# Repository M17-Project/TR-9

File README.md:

# TR-9
<p align='center'>

</p>

TR-9 is a handheld transceiver (HT) for the M17 standard. Its specification can be found [here](https://github.com/sp5wwp/M17_spec).
This repo contains KiCAD schematics and gerber files. 

The firmware source code has been moved to [M17-project/TR-9_firmware](https://github.com/m17-project/TR-9_firmware).
The codeplug example has been moved to [TR-9_Codeplug](https://github.com/M17-Project/codeplug)

# Capabilities
The TR-9 Radio will be capable of the following:
* UHF band (420 MHz - 450 MHz)
* Digital Voice ([M17 Codec](https://docs.m17project.org))
* FM Voice
* APRS via 1200 bps Packet (AX.25)
* Short text messaging (SMS-like)
* Optional Wi-Fi and GPS modules

# Hardware  
The heart of TR-9 is STM32F777VI microcontroller. The handheld also contains:  
*  a **DEM 128128A1 TMH-PWN** 1.44" 128x128px TFT display  
*  an **ESP8266-12F** WiFi module  
*  an **ADF7021** chip for the RF  
*  an **LSM9DS1** 9DoF sensor  
*  a USB-micro connector for firmware update (so-called *DFU mode*)  
*  a microSD card slot for codeplug and storage  
*  a connector for a GNSS module  
*  a Kenwood connector for external MIC/SPK  

RF output level can be regulated by the software. The maximum power output is 3 watts. The radio can work with both analog and digital modulation.  

# Software
M17 standard was designed having [Codec2](https://github.com/drowe67/codec2) vocoder in mind. TR-9 takes advantage of STM's internal Advanced Encryption Standard (AES) hardware for optional end-to-end encryption. There is a possibility of using other block ciphers and scrambling.  

## Pinouts

Mainboard SWD/STLink: [GND, 3v3, CLK, DIO, RST], square pad is Pin 1 and therefore GND.

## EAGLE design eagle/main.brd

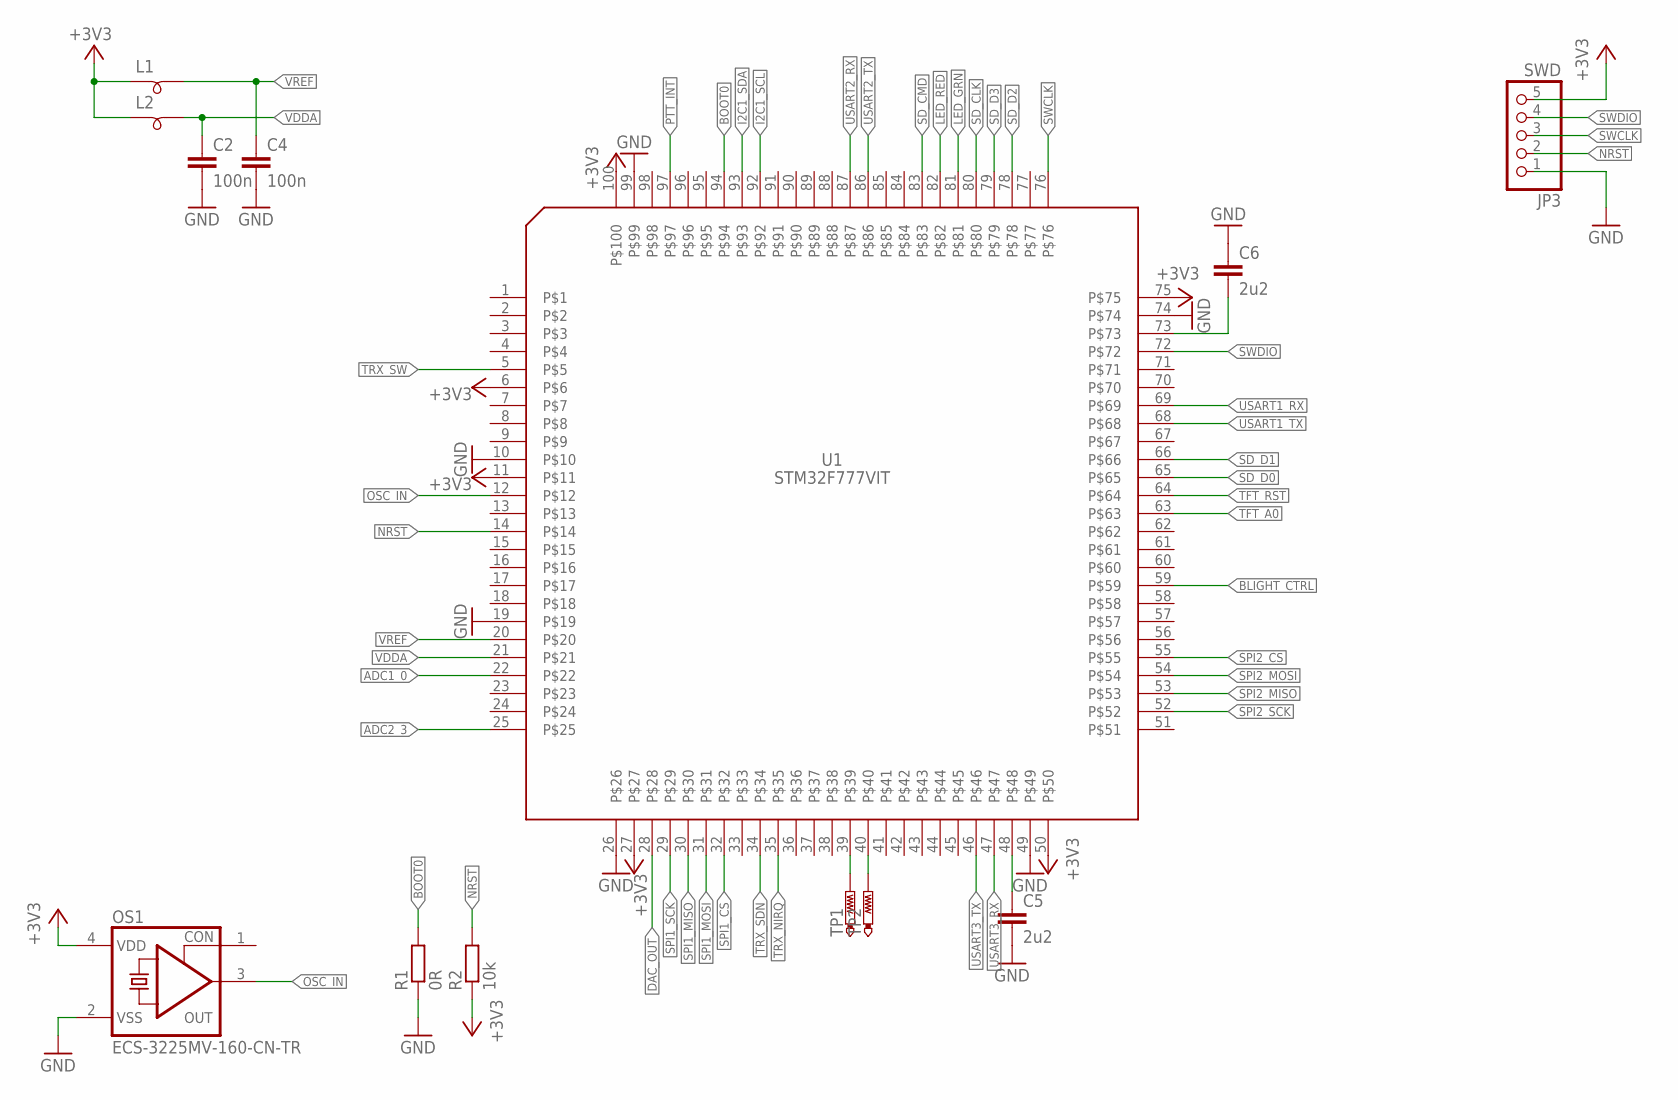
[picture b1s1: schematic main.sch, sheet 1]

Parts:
C2, C4: 100n; C0805
C5, C6: 2u2; C1206
JP3: SWD; 1X05/90
L1, L2: SM-B5
OS1: ECS-3225MV-160-CN-TR; 3.4X2.7-4-PAD
R1: 0R; R0805
R2: 10k; R0805
TP1, TP2: PTR1B1,27; B1,27
U1: STM32F777VIT; LQFP100

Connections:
+3V3: JP3.5, L1.1, L2.1, OS1.4 (VDD), R2.1, U1.6, U1.11, U1.27, U1.50, U1.75, U1.100; also elsewhere on the board
ADC1_0: U1.22; also elsewhere on the board
ADC2_3: U1.25; also elsewhere on the board
BLIGHT_CTRL: U1.59; also elsewhere on the board
BOOT0: R1.2, U1.94
DAC_OUT: U1.28; also elsewhere on the board
GND: C2.2, C4.2, C5.2, C6.1, JP3.1, OS1.2 (VSS), R1.1, U1.10, U1.19, U1.26, U1.49, U1.74, U1.99; also elsewhere on the board
I2C1_SCL: U1.92; also elsewhere on the board
I2C1_SDA: U1.93; also elsewhere on the board
LED_GRN: U1.81; also elsewhere on the board
LED_RED: U1.82; also elsewhere on the board
unnamed: C6.2, U1.73
unnamed: C5.1, U1.48
unnamed: TP1.TP, U1.39
unnamed: TP2.TP, U1.40
NRST: JP3.2, R2.2, U1.14
OSC_IN: OS1.3 (OUT), U1.12
PTT_INT: U1.97; also elsewhere on the board
SD_CLK: U1.80; also elsewhere on the board
SD_CMD: U1.83; also elsewhere on the board
SD_D0: U1.65; also elsewhere on the board
SD_D1: U1.66; also elsewhere on the board
SD_D2: U1.78; also elsewhere on the board
SD_D3: U1.79; also elsewhere on the board
SPI1_CS: U1.32; also elsewhere on the board
SPI1_MISO: U1.30
SPI1_MOSI: U1.31; also elsewhere on the board
SPI1_SCK: U1.29; also elsewhere on the board
SPI2_CS: U1.55; also elsewhere on the board
SPI2_MISO: U1.53; also elsewhere on the board
SPI2_MOSI: U1.54; also elsewhere on the board
SPI2_SCK: U1.52; also elsewhere on the board
SWCLK: JP3.3, U1.76
SWDIO: JP3.4, U1.72
TFT_A0: U1.63; also elsewhere on the board
TFT_RST: U1.64; also elsewhere on the board
TRX_NIRQ: U1.35; also elsewhere on the board
TRX_SDN: U1.34; also elsewhere on the board
TRX_SW: U1.5; also elsewhere on the board
USART1_RX: U1.69; also elsewhere on the board
USART1_TX: U1.68
USART2_RX: U1.87; also elsewhere on the board
USART2_TX: U1.86; also elsewhere on the board
USART3_RX: U1.47; also elsewhere on the board
USART3_TX: U1.46
VDDA: C2.1, L2.2, U1.21
VREF: C4.1, L1.2, U1.20

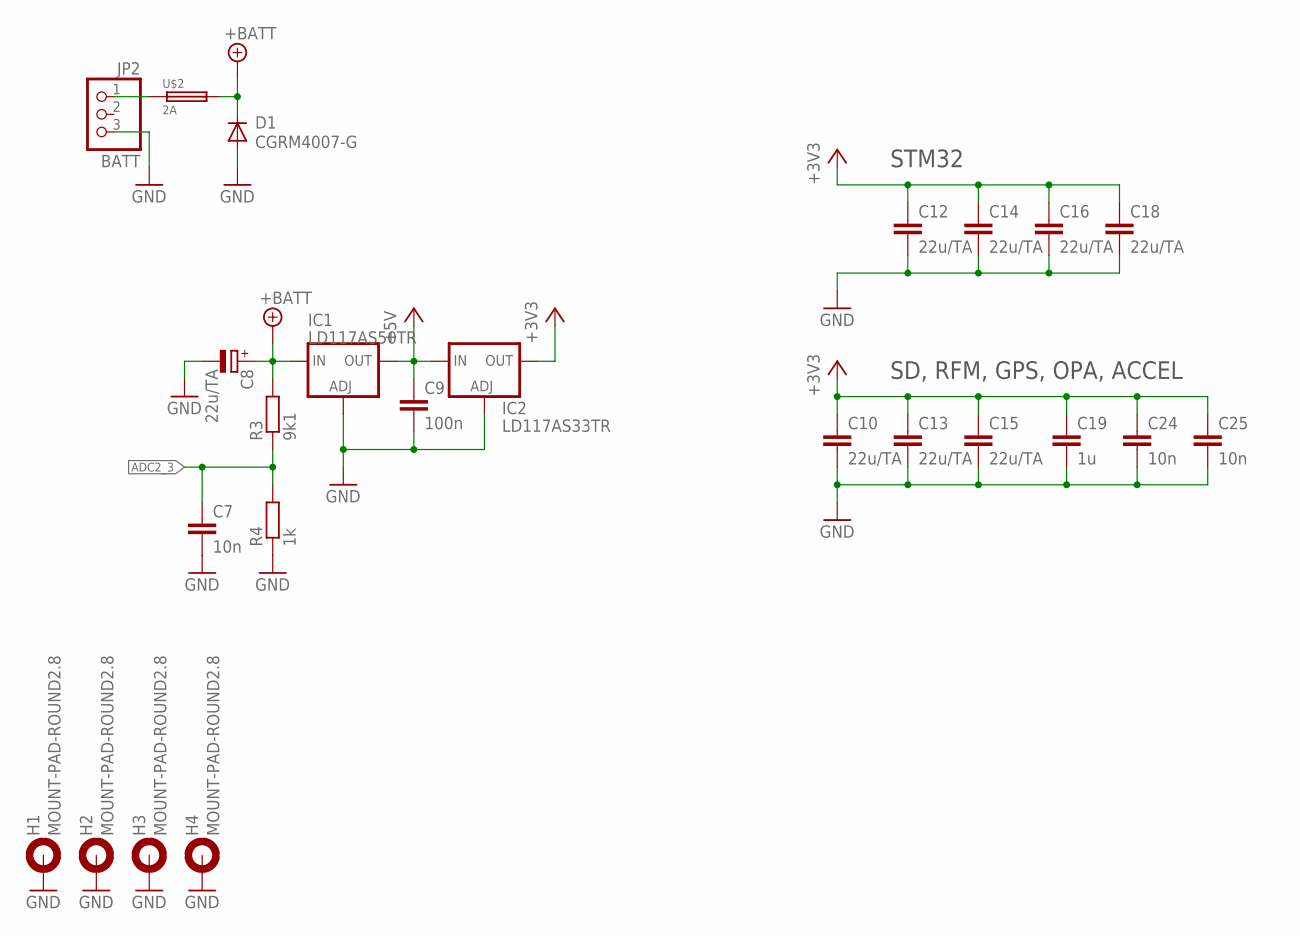
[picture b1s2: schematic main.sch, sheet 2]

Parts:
C7, C24, C25: 10n; C0805
C8: 22u/TA; SMC_C
C9: 100n; C1206
C10, C12, C13, C14, C15, C16, C18: 22u/TA; C1206
C19: 1u; C1206
D1: CGRM4007-G; SOD-123_MINI-SMA
H1, H2, H3, H4: MOUNT-PAD-ROUND2.8; 2,8-PAD
IC1: LD117AS50TR; SOT223
IC2: LD117AS33TR; SOT223
JP2: BATT; 1X03/90
R3: 9k1; R0805
R4: 1k; R0805
U$2: 2A; 1206

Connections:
+3V3: C10.1, C12.1, C13.1, C14.1, C15.1, C16.1, C18.1, C19.1, C24.1, C25.1, IC2.4 (OUT); also elsewhere on the board
+5V: C9.1, IC1.4 (OUT), IC2.3 (IN)
+BATT: C8.+, D1.C, IC1.3 (IN), R3.2, U$2.2; also elsewhere on the board
ADC2_3: C7.1, R3.1, R4.2; also elsewhere on the board
GND: C7.2, C8.-, C9.2, C10.2, C12.2, C13.2, C14.2, C15.2, C16.2, C18.2, C19.2, C24.2, C25.2, D1.A, H1.B2,8, H2.B2,8, H3.B2,8, H4.B2,8, IC1.1 (ADJ), IC2.1 (ADJ), JP2.3, R4.1; also elsewhere on the board
unnamed: JP2.1, U$2.1

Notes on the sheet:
STM32
SD, RFM, GPS, OPA, ACCEL

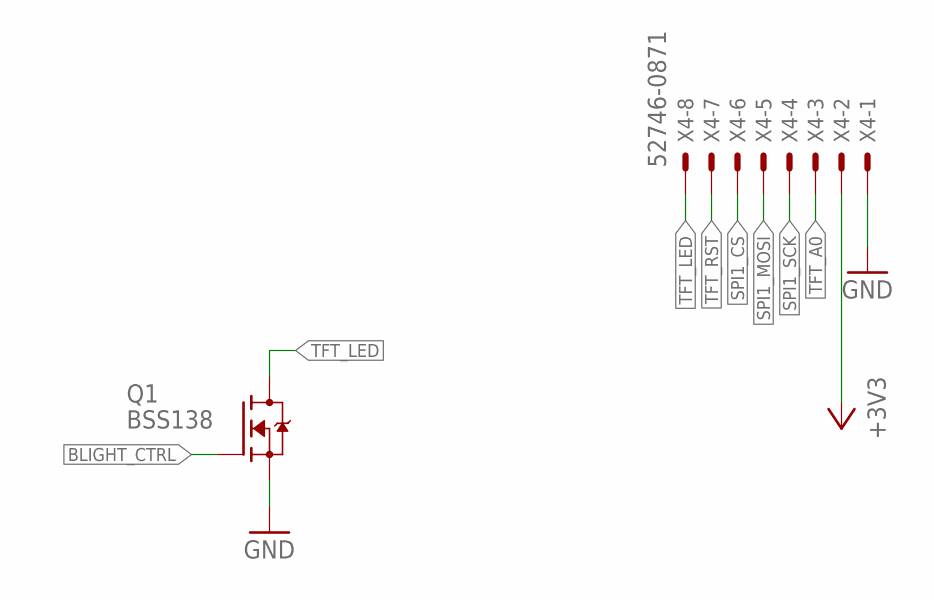
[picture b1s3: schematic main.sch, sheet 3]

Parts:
Q1: BSS138; SOT23
X4: 52746-0871; 52745-0890

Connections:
+3V3: X4.2; also elsewhere on the board
BLIGHT_CTRL: Q1.1 (G); also elsewhere on the board
GND: Q1.2 (S), X4.1; also elsewhere on the board
SPI1_CS: X4.6; also elsewhere on the board
SPI1_MOSI: X4.5; also elsewhere on the board
SPI1_SCK: X4.4; also elsewhere on the board
TFT_A0: X4.3; also elsewhere on the board
TFT_LED: Q1.3 (D), X4.8
TFT_RST: X4.7; also elsewhere on the board

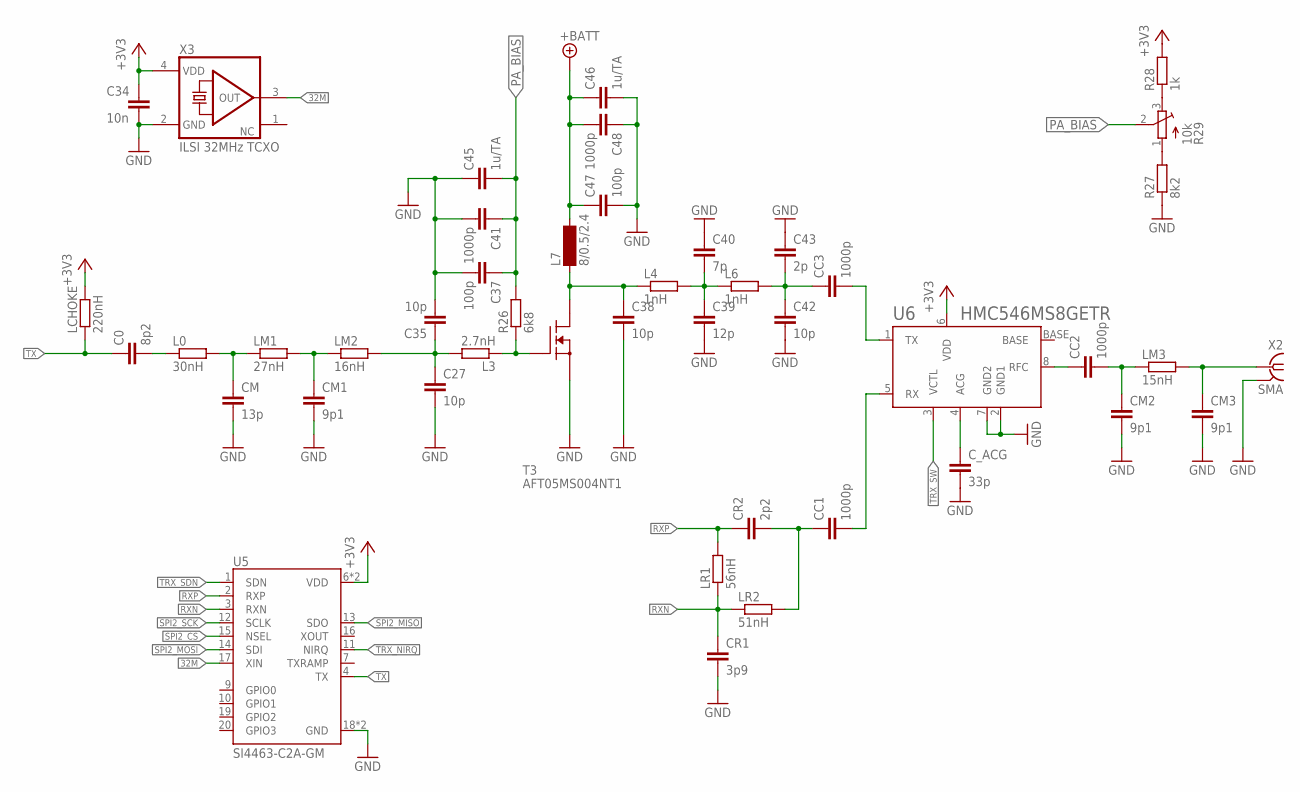
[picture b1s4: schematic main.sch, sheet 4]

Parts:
C0: 8p2; C0805
C27, C35, C38, C42: 10p; C0805
C34: 10n; C0805
C37, C47: 100p; C0805
C39: 12p; C0805
C40: 7p; C0805
C41, C48: 1000p; C0805
C43: 2p; C0805
C45, C46: 1u/TA; C1206
CC1, CC2, CC3: 1000p; C0805
CM: 13p; C0805
CM1, CM2, CM3: 9p1; C0805
CR1: 3p9; C0805
CR2: 2p2; C0805
C_ACG: 33p; C0805
L0: 30nH; R0805
L3: 2.7nH; R0805
L4, L6: 1nH; R0603
L7: 8/0.5/2.4; SM-L15B
LCHOKE: 220nH; R0805
LM1: 27nH; R0805
LM2: 16nH; R0805
LM3: 15nH; R0805
LR1: 56nH; R0805
LR2: 51nH; R0805
R26: 6k8; R0805
R27: 8k2; R0805
R28: 1k; R0805
R29: 10k; 3223W
T3: AFT05MS004NT1; SOT89-BCE
U5: SI4463-C2A-GM; QFN50P400X400X90-20N
U6: HMC546MS8GETR; SOP65P490X110-8N
X2: SMA; J502-ND-142-0701-871/876
X3: ILSI 32MHz TCXO; ASE

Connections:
32M: U5.17 (XIN), X3.3 (OUT)
+3V3: C34.1, LCHOKE.2, R28.2, U5.6 (VDD), U5.8 (VDD), U6.6 (VDD), X3.4 (VDD); also elsewhere on the board
+BATT: C46.1, C47.1, C48.2, L7.2; also elsewhere on the board
GND: C27.2, C34.2, C35.2, C37.2, C38.2, C39.2, C40.1, C41.2, C42.2, C43.1, C45.1, C46.2, C47.2, C48.1, CM.2, CM1.2, CM2.2, CM3.2, CR1.2, C_ACG.2, R27.1, T3.S, U5.18 (GND), U5.21 (GND), U6.2 (GND1), U6.7 (GND2), X2.G@1 (2), X2.G@2 (2), X2.G@3 (2), X2.G@4 (2), X3.2 (GND); also elsewhere on the board
unnamed: CC3.2, U6.1 (TX)
unnamed: C27.1, C35.1, L3.2, LM2.2
unnamed: CM3.1, LM3.2, X2.1
unnamed: CC2.2, CM2.1, LM3.1
unnamed: C0.2, L0.1
unnamed: CM.1, L0.2, LM1.1
unnamed: CM1.1, LM1.2, LM2.1
unnamed: R27.2, R29.1 (A)
unnamed: CC1.1, CR2.2, LR2.2
unnamed: L3.1, R26.1, T3.G
unnamed: CC1.2, U6.5 (RX)
unnamed: CC2.1, U6.8 (RFC)
unnamed: C_ACG.1, U6.4 (ACG)
unnamed: R28.1, R29.3 (E)
unnamed: C38.1, L4.1, L7.1, T3.D
unnamed: C39.1, C40.2, L4.2, L6.1
unnamed: C42.1, C43.2, CC3.1, L6.2
PA_BIAS: C37.1, C41.1, C45.2, R26.2, R29.2 (S)
RXN: CR1.1, LR1.1, LR2.1, U5.3 (RXN)
RXP: CR2.1, LR1.2, U5.2 (RXP)
SPI2_CS: U5.15 (NSEL); also elsewhere on the board
SPI2_MISO: U5.13 (SDO); also elsewhere on the board
SPI2_MOSI: U5.14 (SDI); also elsewhere on the board
SPI2_SCK: U5.12 (SCLK); also elsewhere on the board
TRX_NIRQ: U5.11 (NIRQ); also elsewhere on the board
TRX_SDN: U5.1 (SDN); also elsewhere on the board
TRX_SW: U6.3 (VCTL); also elsewhere on the board
TX: C0.1, LCHOKE.1, U5.4 (TX)

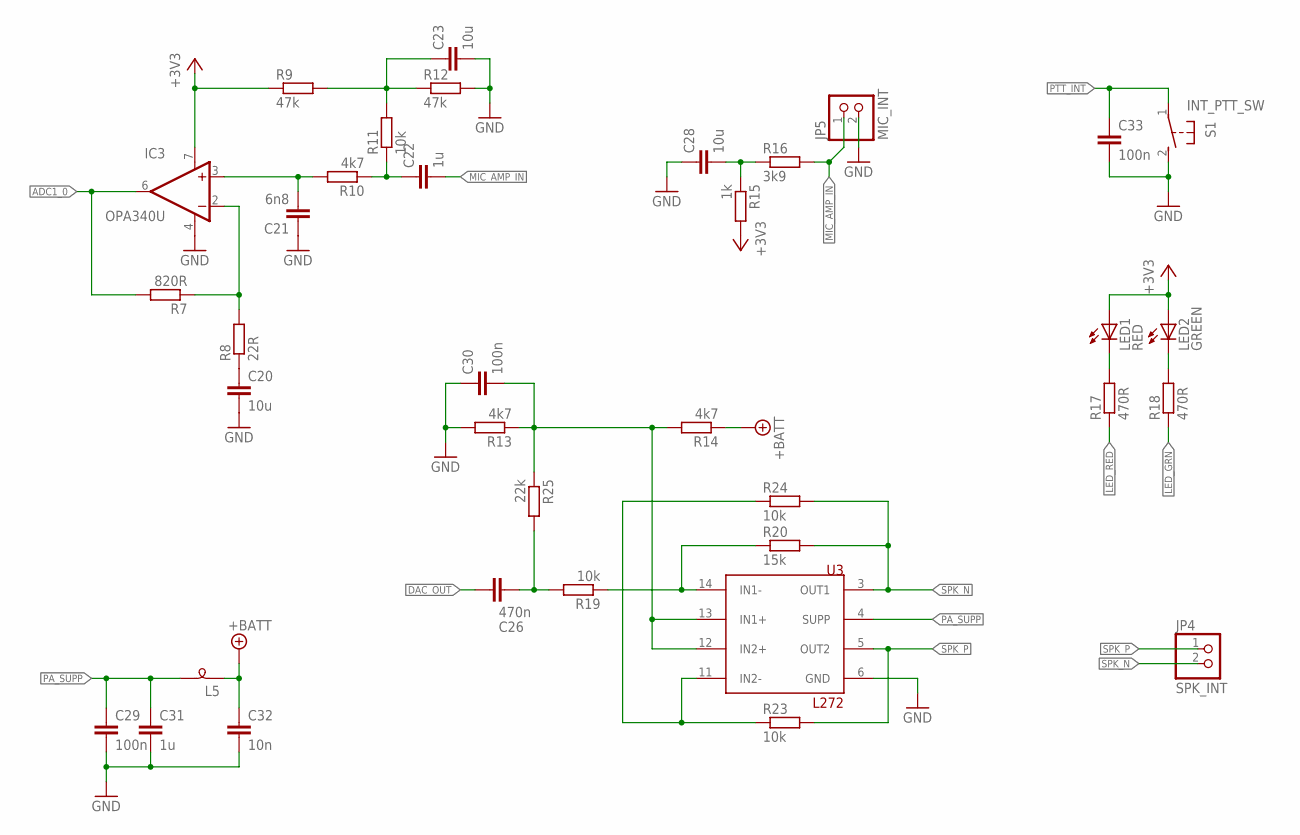
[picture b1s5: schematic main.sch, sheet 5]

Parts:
C20, C23, C28: 10u; C1206
C21: 6n8; C0805
C22, C31: 1u; C1206
C26: 470n; C0805
C29, C30: 100n; C1206
C32: 10n; C0805
C33: 100n; C0805
IC3: OPA340U; SO08
JP4: SPK_INT; 1X02
JP5: MIC_INT; 1X02
L5: SM-B5
LED1: RED; CHIPLED_1206
LED2: GREEN; CHIPLED_1206
R7: 820R; R0805
R8: 22R; R0805
R9, R12: 47k; R0805
R10, R13, R14: 4k7; R0805
R11, R19, R23, R24: 10k; R0805
R15: 1k; R0805
R16: 3k9; R0805
R17, R18: 470R; R0805
R20: 15k; R0805
R25: 22k; R0805
S1: INT_PTT_SW; B3F-31XX
U3: L272; SO16

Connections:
+3V3: IC3.7 (V+), LED1.A, LED2.A, R9.1, R15.2; also elsewhere on the board
+BATT: C32.1, L5.1, R14.1; also elsewhere on the board
ADC1_0: IC3.6 (OUT), R7.2; also elsewhere on the board
DAC_OUT: C26.1; also elsewhere on the board
GND: C20.2, C21.1, C23.2, C28.1, C29.2, C30.1, C31.2, C32.2, C33.2, IC3.4 (V-), JP5.2, R12.2, R13.2, S1.2 (S), U3.6 (GND); also elsewhere on the board
LED_GRN: R18.1; also elsewhere on the board
LED_RED: R17.1; also elsewhere on the board
MIC_AMP_IN: C22.2, JP5.1, R16.2
unnamed: R19.1, R20.1, U3.14 (IN1-)
unnamed: IC3.2 (-IN), R7.1, R8.2
unnamed: C22.1, R10.1, R11.1
unnamed: C20.1, R8.1
unnamed: LED1.C, R17.2
unnamed: LED2.C, R18.2
unnamed: R23.1, R24.1, U3.11 (IN2-)
unnamed: C26.2, R19.2, R25.2
unnamed: C28.2, R15.1, R16.1
unnamed: C21.2, IC3.3 (+IN), R10.2
unnamed: C23.1, R9.2, R11.2, R12.1
unnamed: C30.2, R13.1, R14.2, R25.1, U3.12 (IN2+), U3.13 (IN1+)
PA_SUPP: C29.1, C31.1, L5.2, U3.4 (SUPP)
PTT_INT: C33.1, S1.1; also elsewhere on the board
SPK_N: JP4.2, R20.2, R24.2, U3.3 (OUT1)
SPK_P: JP4.1, R23.2, U3.5 (OUT2)

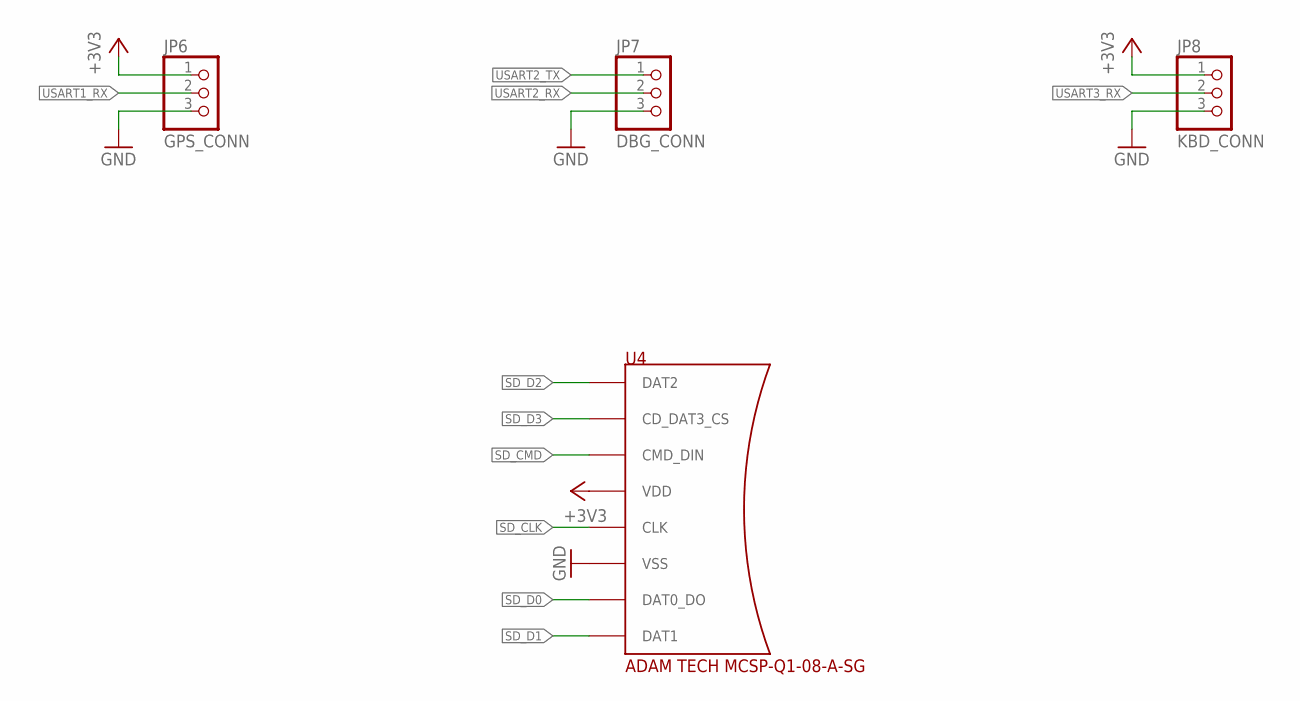
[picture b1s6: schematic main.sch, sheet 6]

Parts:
JP6: GPS_CONN; 1X03
JP7: DBG_CONN; 1X03
JP8: KBD_CONN; 1X03
U4: ADAM TECH MCSP-Q1-08-A-SG; MICROSD-PUSH-OUT

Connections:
+3V3: JP6.1, JP8.1, U4.4 (VDD); also elsewhere on the board
GND: JP6.3, JP7.3, JP8.3, U4.6 (VSS), U4.G1 (VSS), U4.G2 (VSS), U4.G3 (VSS), U4.G4 (VSS); also elsewhere on the board
SD_CLK: U4.5 (CLK); also elsewhere on the board
SD_CMD: U4.3 (CMD_DIN); also elsewhere on the board
SD_D0: U4.7 (DAT0_DO); also elsewhere on the board
SD_D1: U4.8 (DAT1); also elsewhere on the board
SD_D2: U4.1 (DAT2); also elsewhere on the board
SD_D3: U4.2 (CD_DAT3_CS); also elsewhere on the board
USART1_RX: JP6.2; also elsewhere on the board
USART2_RX: JP7.2; also elsewhere on the board
USART2_TX: JP7.1; also elsewhere on the board
USART3_RX: JP8.2; also elsewhere on the board

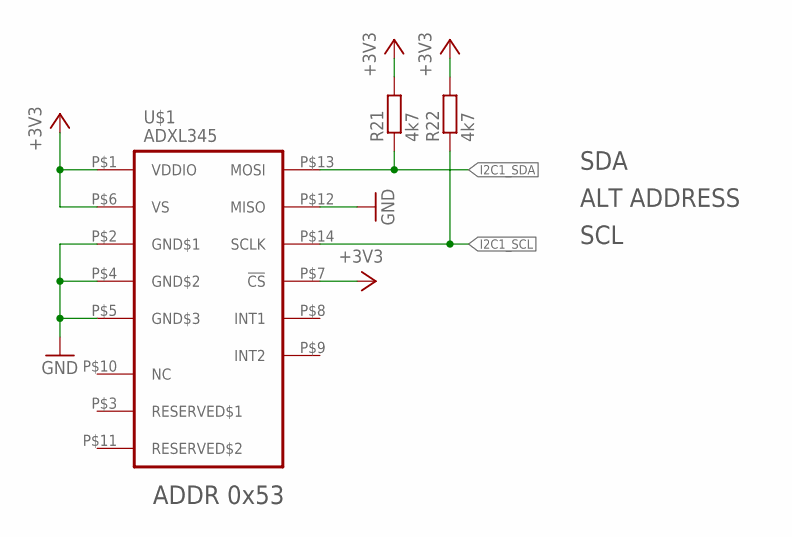
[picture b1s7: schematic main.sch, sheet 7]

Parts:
R21, R22: 4k7; R0805
U$1: ADXL345; LGA14

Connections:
+3V3: R21.2, R22.2, U$1.P$1 (VDDIO), U$1.P$6 (VS), U$1.P$7 (!CS); also elsewhere on the board
GND: U$1.P$2 (GND$1), U$1.P$4 (GND$2), U$1.P$5 (GND$3), U$1.P$12 (MISO); also elsewhere on the board
I2C1_SCL: R22.1, U$1.P$14 (SCLK); also elsewhere on the board
I2C1_SDA: R21.1, U$1.P$13 (MOSI); also elsewhere on the board

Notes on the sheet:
ALT ADDRESS
SDA
SCL
ADDR 0x53

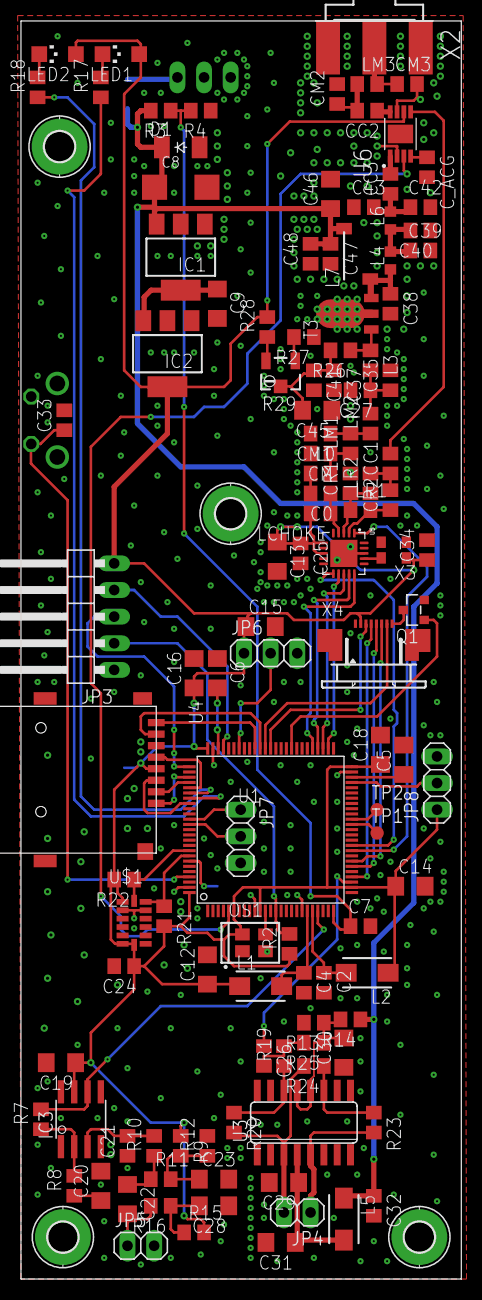
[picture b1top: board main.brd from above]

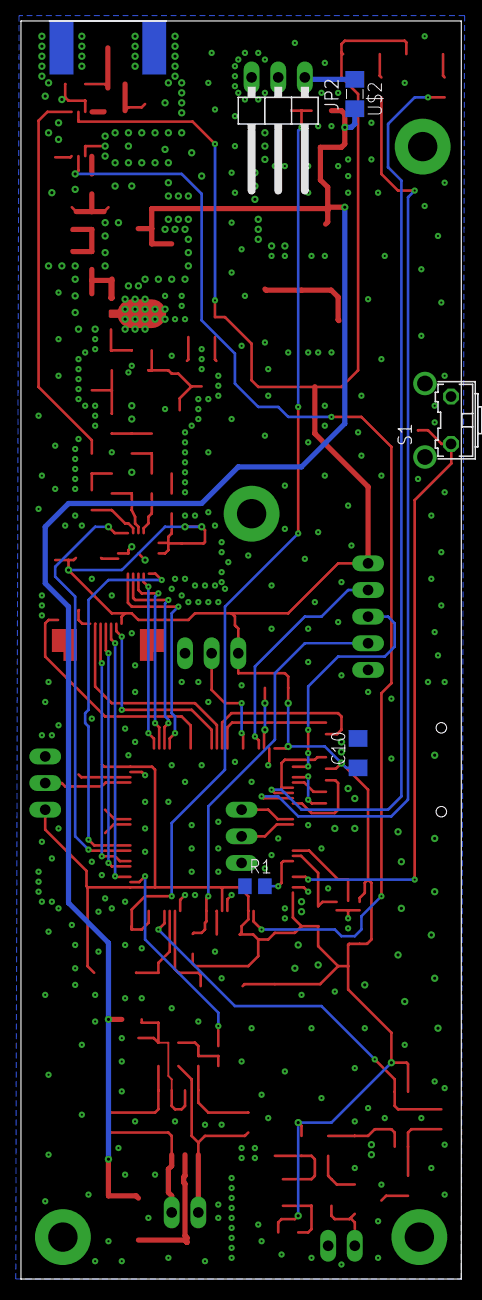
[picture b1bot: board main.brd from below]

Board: 2 copper layers, 42.0 x 120.0 mm, 127 parts (5 on the bottom side), 86 nets.

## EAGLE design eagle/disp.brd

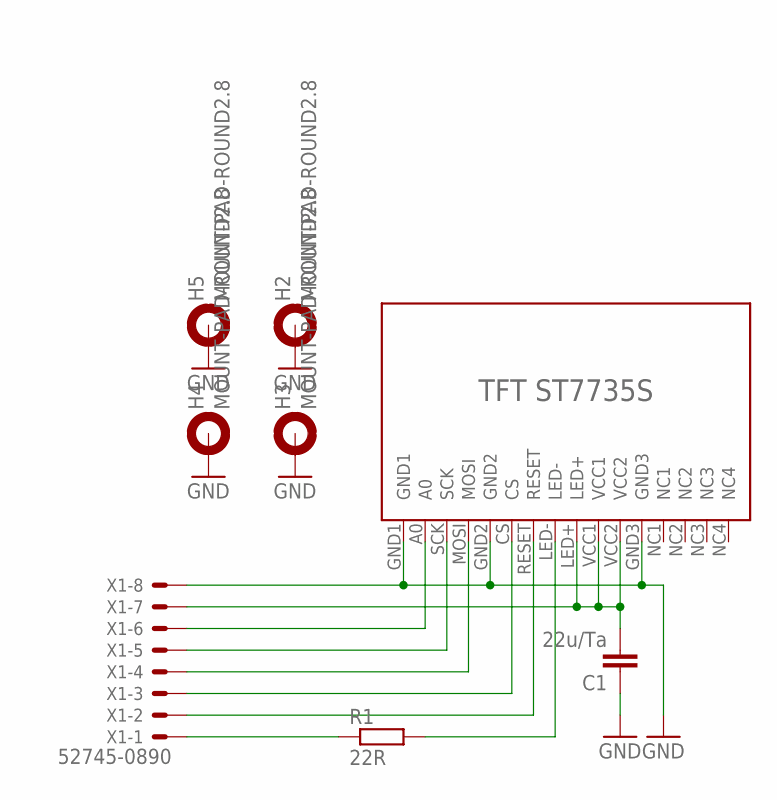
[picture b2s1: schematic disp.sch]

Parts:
C1: 22u/Ta; C1206
H2, H3, H4, H5: MOUNT-PAD-ROUND2.8; 2,8-PAD
R1: 22R; R0805
U$1: TFT_ST7735S
X1: 52745-0890

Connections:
GND: C1.1, H2.B2,8, H3.B2,8, H4.B2,8, H5.B2,8, U$1.GND1, U$1.GND2, U$1.GND3, X1.8
unnamed: C1.2, U$1.LED+, U$1.VCC1, U$1.VCC2, X1.7
unnamed: U$1.A0, X1.6
unnamed: U$1.SCK, X1.5
unnamed: U$1.MOSI, X1.4
unnamed: U$1.CS, X1.3
unnamed: U$1.RESET, X1.2
unnamed: R1.1, X1.1
unnamed: R1.2, U$1.LED-

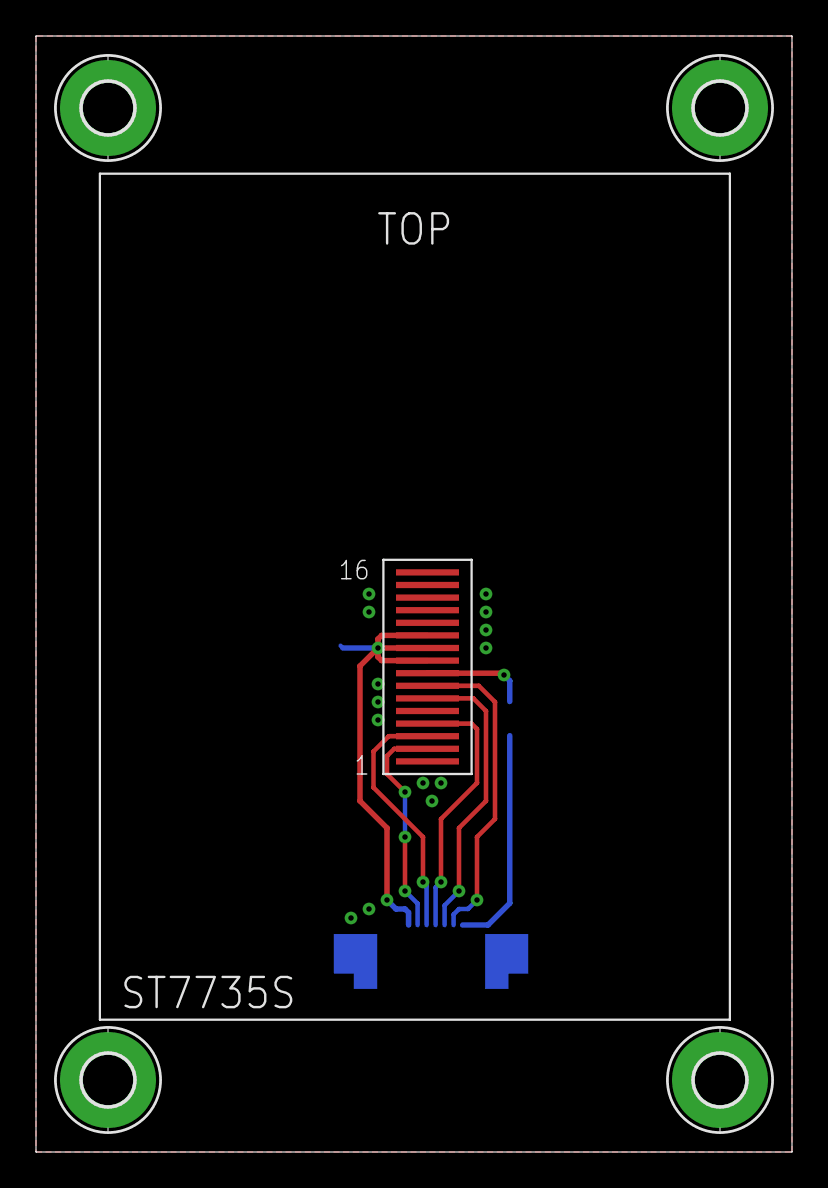
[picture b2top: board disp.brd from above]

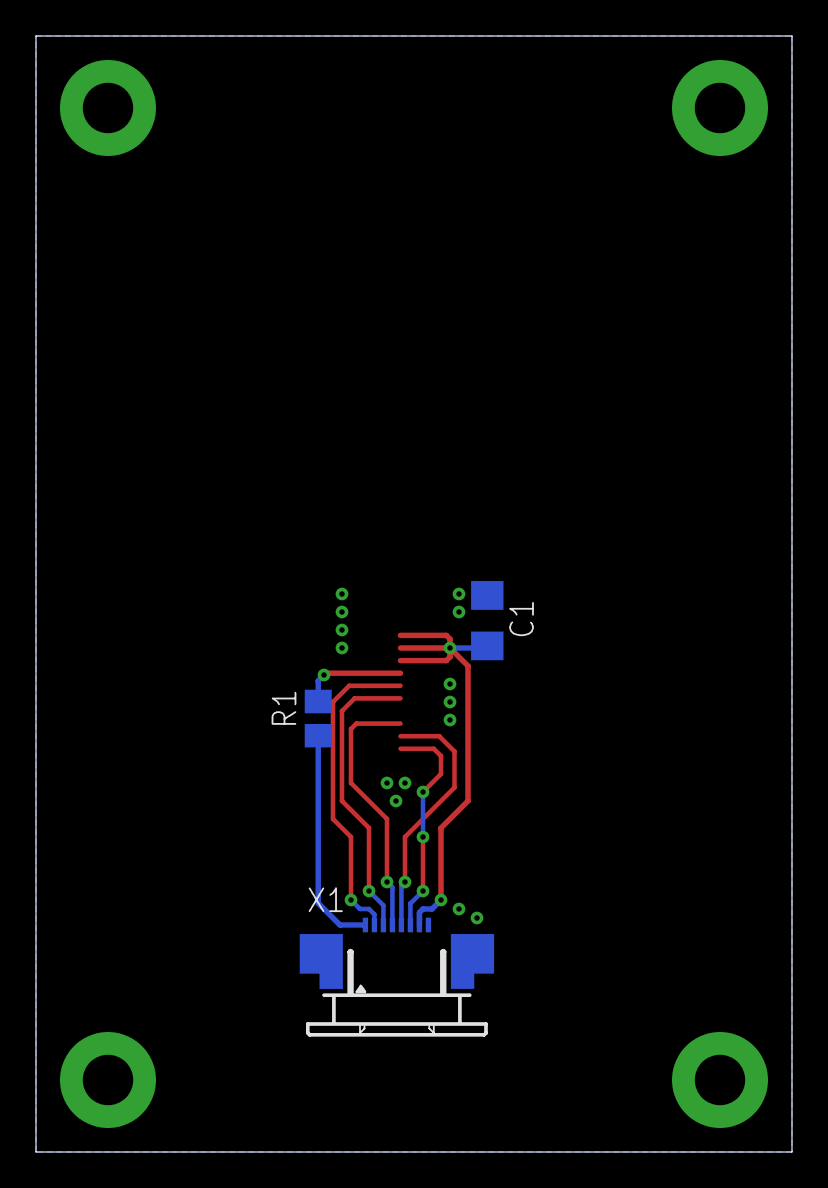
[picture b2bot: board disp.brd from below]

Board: 2 copper layers, 42.0 x 62.0 mm, 8 parts (3 on the bottom side), 9 nets.

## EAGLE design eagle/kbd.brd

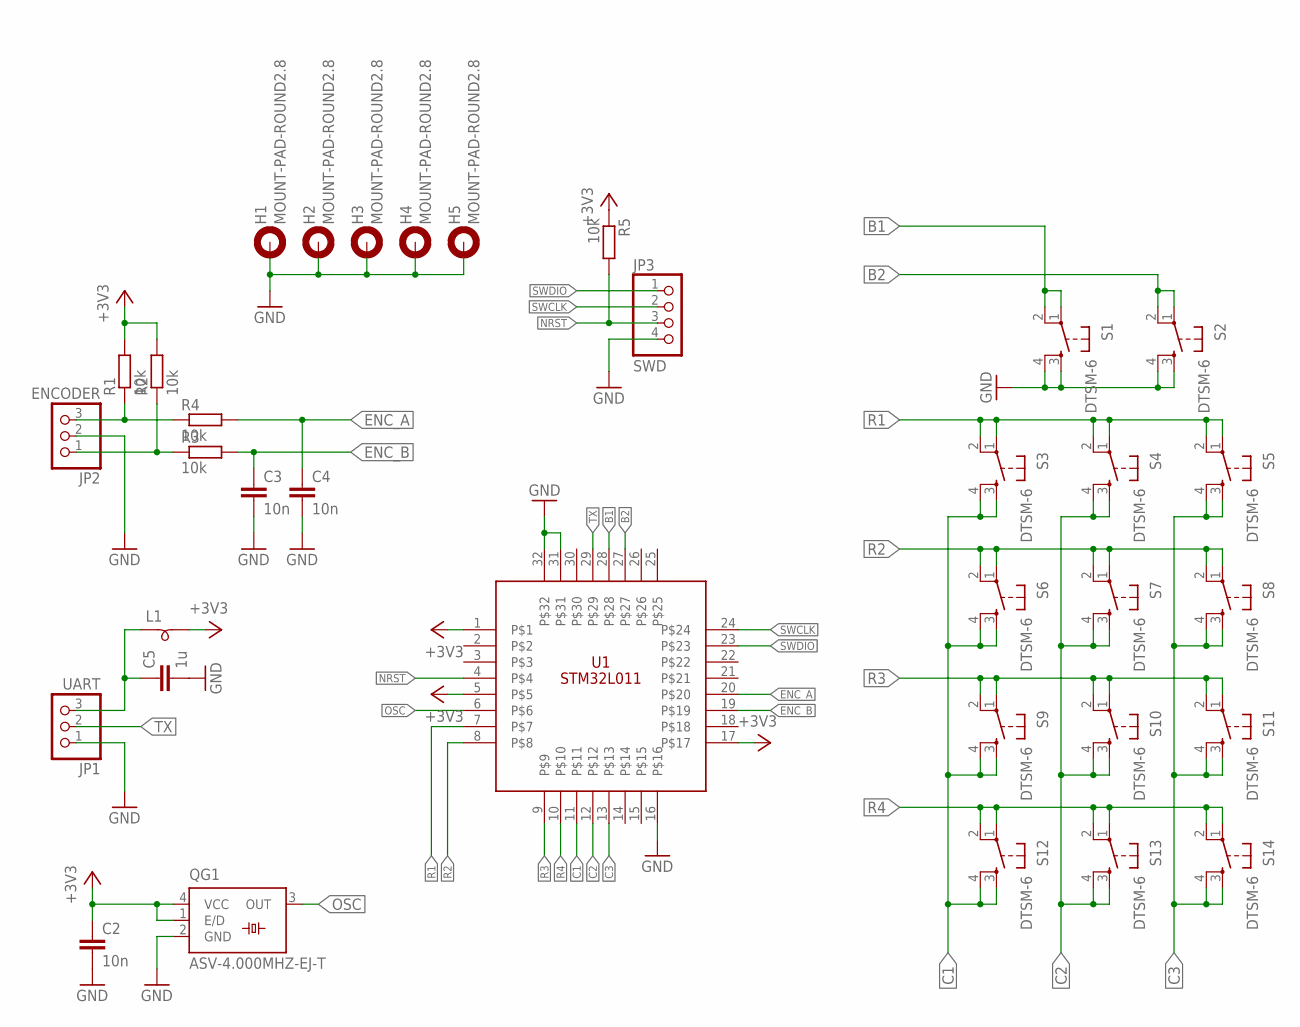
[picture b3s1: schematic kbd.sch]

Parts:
C2, C3, C4: 10n; C0805
C5: 1u; C1206
H1, H2, H3, H4, H5: MOUNT-PAD-ROUND2.8; 2,8-PAD
JP1: UART; 1X03
JP2: ENCODER; 1X03
JP3: SWD; 1X04
L1: SM-B5
QG1: ASV-4.000MHZ-EJ-T; SM77H
R1, R2, R3, R4, R5: 10k; R0805
S1, S2, S3, S4, S5, S6, S7, S8, S9, S10, S11, S12, S13, S14: DTSM-6
U1: STM32L011; LQFP32-7X7

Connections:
+3V3: C2.1, L1.2, QG1.1 (E/D), QG1.4 (VCC), R1.2, R2.2, R5.1, U1.1, U1.5, U1.17
B1: S1.1, S1.2, U1.28
B2: S2.1, S2.2, U1.27
C1: S3.3, S3.4, S6.3, S6.4, S9.3, S9.4, S12.3, S12.4, U1.11
C2: S4.3, S4.4, S7.3, S7.4, S10.3, S10.4, S13.3, S13.4, U1.12
C3: S5.3, S5.4, S8.3, S8.4, S11.3, S11.4, S14.3, S14.4, U1.13
ENC_A: C4.1, R4.2, U1.20
ENC_B: C3.1, R3.2, U1.19
GND: C2.2, C3.2, C4.2, C5.2, H1.B2,8, H2.B2,8, H3.B2,8, H4.B2,8, H5.B2,8, JP1.1, JP2.2, JP3.4, QG1.2 (GND), S1.3, S1.4, S2.3, S2.4, U1.16, U1.31, U1.32
unnamed: JP2.3, R1.1, R4.1
unnamed: JP2.1, R2.1, R3.1
unnamed: C5.1, JP1.3, L1.1
NRST: JP3.3, R5.2, U1.4
OSC: QG1.3 (OUT), U1.6
R1: S3.1, S3.2, S4.1, S4.2, S5.1, S5.2, U1.7
R2: S6.1, S6.2, S7.1, S7.2, S8.1, S8.2, U1.8
R3: S9.1, S9.2, S10.1, S10.2, S11.1, S11.2, U1.9
R4: S12.1, S12.2, S13.1, S13.2, S14.1, S14.2, U1.10
SWCLK: JP3.2, U1.24
SWDIO: JP3.1, U1.23
TX: JP1.2, U1.29

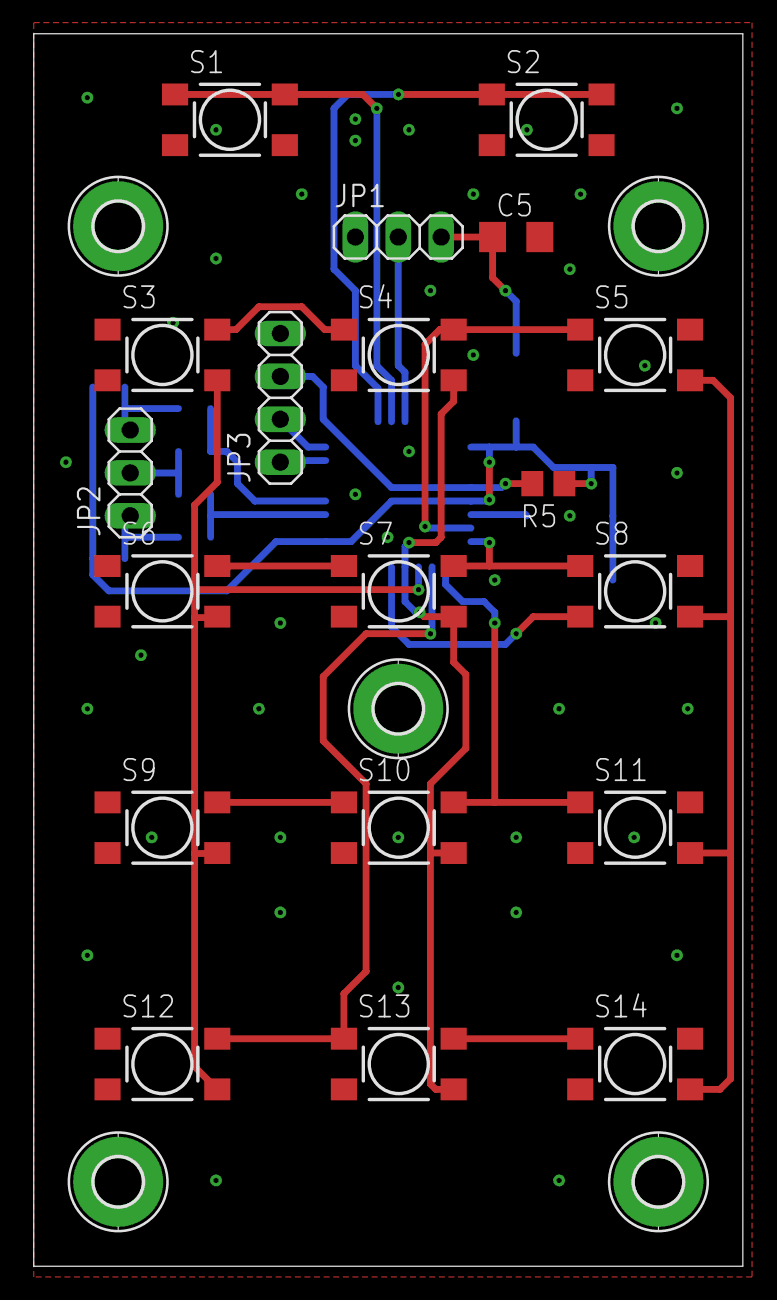
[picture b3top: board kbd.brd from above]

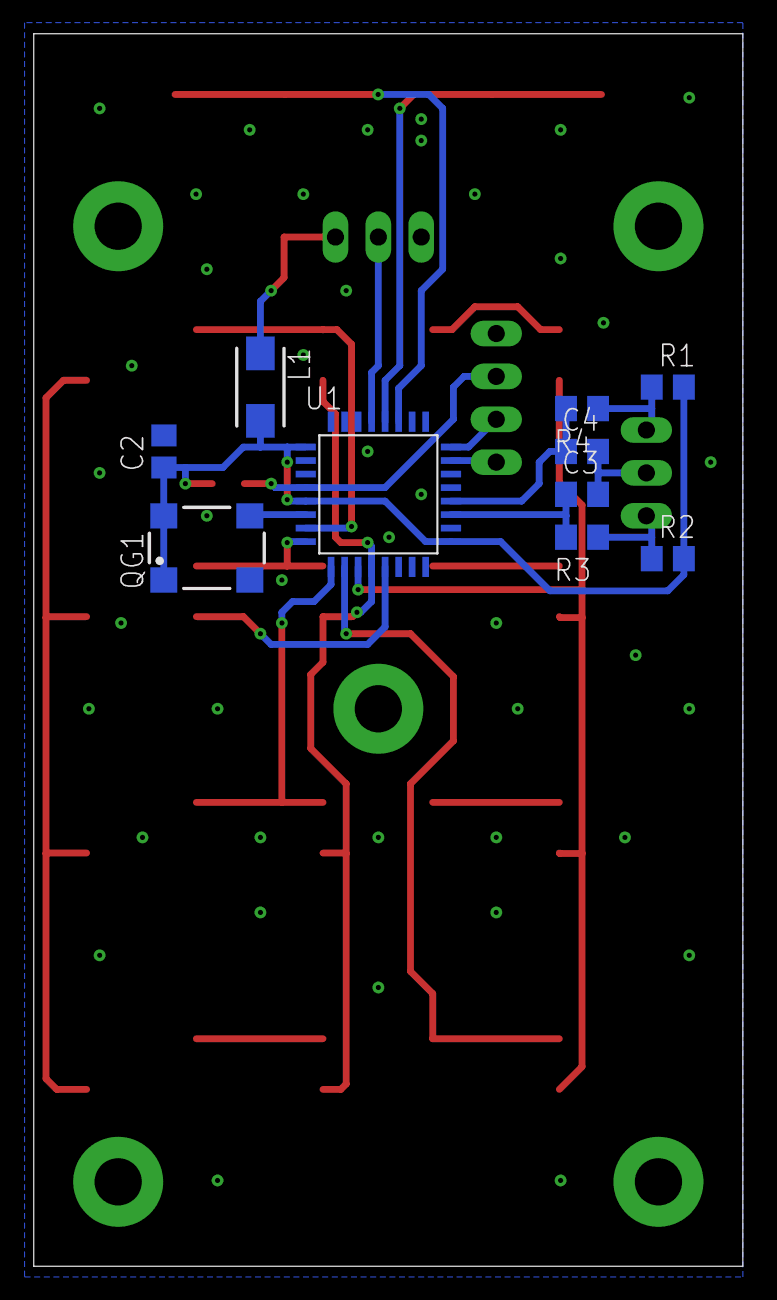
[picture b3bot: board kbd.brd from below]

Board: 2 copper layers, 42.0 x 73.0 mm, 34 parts (10 on the bottom side), 21 nets.
